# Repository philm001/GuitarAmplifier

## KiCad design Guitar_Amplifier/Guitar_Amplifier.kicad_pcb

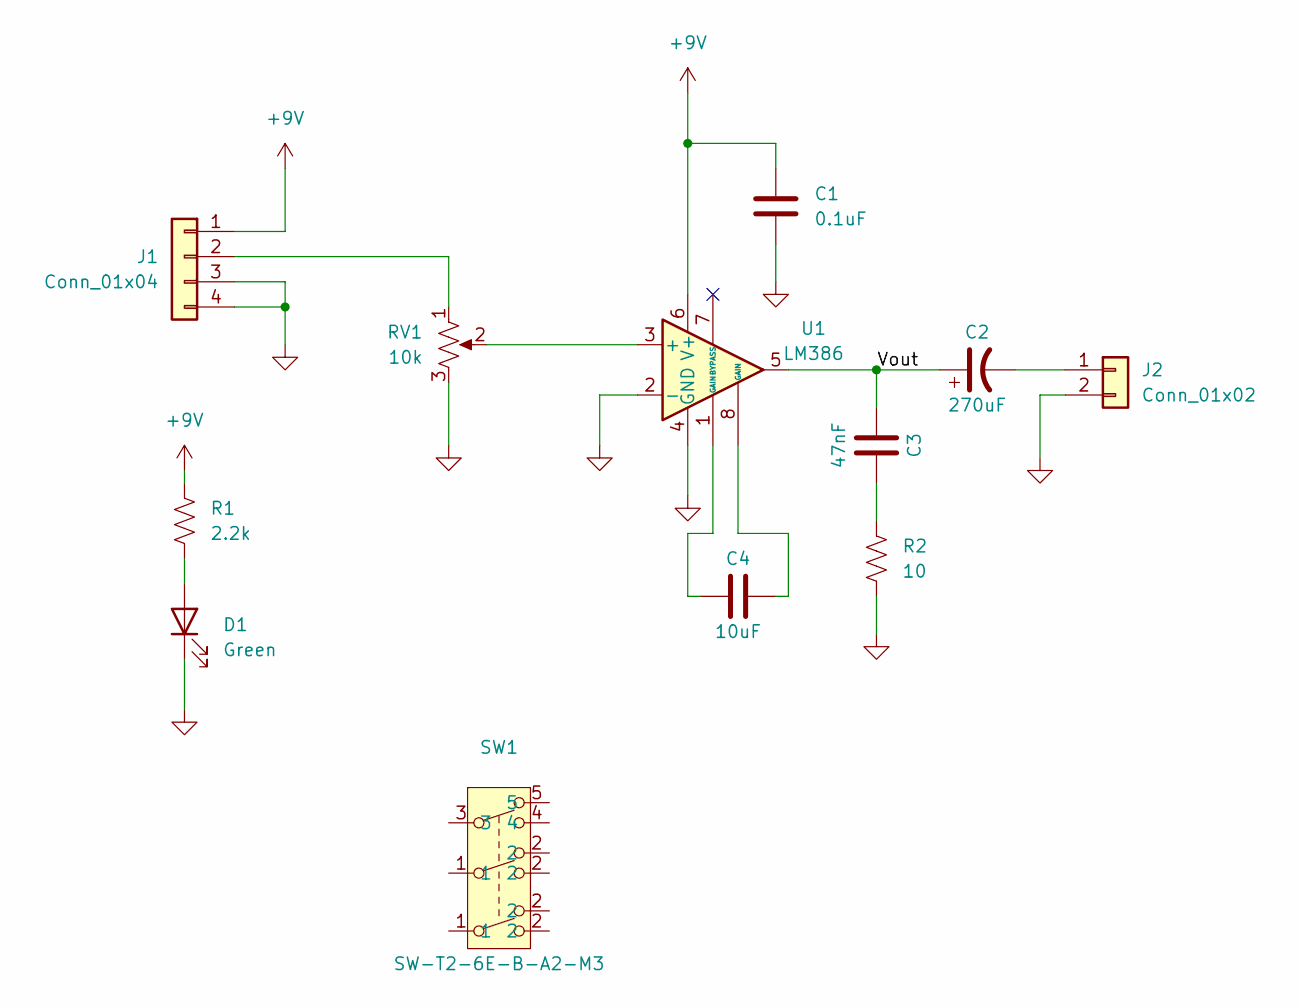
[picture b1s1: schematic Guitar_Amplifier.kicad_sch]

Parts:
C1: 0.1uF; C_0603_1608Metric; Mfg. PN CL10B104KA8NNNC
C2: 270uF; CP_Elec_10x10; Mfg. PN GYB1E271MCQ1GS
C3: 47nF; C_0603_1608Metric; Mfg. PN CL10B473KA8WPNC
C4: 10uF; C_0603_1608Metric; Mfg. PN CL10A106MA8NRNC
D1: Green; D_0805_2012Metric; Mfg. PN 150080VS75000
J1: Conn_01x04; PinHeader_1x04_P1.00mm_Vertical
J2: Conn_01x02; PinHeader_1x02_P1.00mm_Vertical
R1: 2.2k; R_0603_1608Metric; Mfg. PN RMCF0603FT2K20
R2: 10; R_0603_1608Metric; Mfg. PN RMCF0603FT10R0
RV1: 10k; Potentiometer_Bourns_TC33X_Vertical; Mfg. PN TC33X-2-103E
SW1: Mfg. PN SW-T2-6E-B-A2-M3
U1: LM386; SOIC-8_3.9x4.9mm_P1.27mm; Mfg. PN LM386M-1/NOPB

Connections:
+9V: C1.1, J1.1, R1.1, U1.6 (V+)
/Vout: C2.1, C3.2, U1.5
GND: C1.2, D1.1 (K), J1.3, J1.4, J2.2, R2.2, RV1.3, U1.2 (-), U1.4 (GND)
unnamed: C3.1, R2.1
unnamed: C4.1, U1.1 (GAIN)
unnamed: C4.2, U1.8 (GAIN)
unnamed: D1.2 (A), R1.2
unnamed: J1.2, RV1.1
unnamed: C2.2, J2.1
unnamed: RV1.2, U1.3 (+)

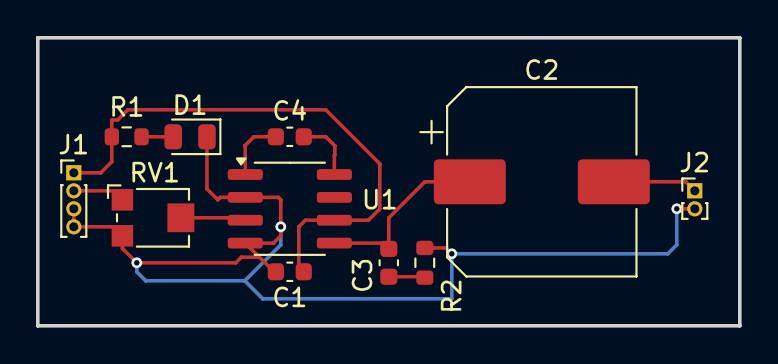
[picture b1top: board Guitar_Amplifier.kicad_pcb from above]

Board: 2 copper layers, 39.0 x 16.0 mm, 11 parts (0 on the bottom side), 10 nets.

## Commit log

2024-02-24 Created initial design files
2024-02-24 Initial schematic creation
2024-02-24 First version of board layout
2024-02-25 Created gerbers, Added GND copper pour
2024-03-02 Added 3PDT Switch
2024-03-04 Added in switch symbol and footprint
2024-03-14 Added additional symbols
